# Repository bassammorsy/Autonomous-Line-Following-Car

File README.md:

# Autonomous-Line-Following-Car
Autonomous line-following robot with KiCad sensor array PCB design and PID motor control firmware on Arduino

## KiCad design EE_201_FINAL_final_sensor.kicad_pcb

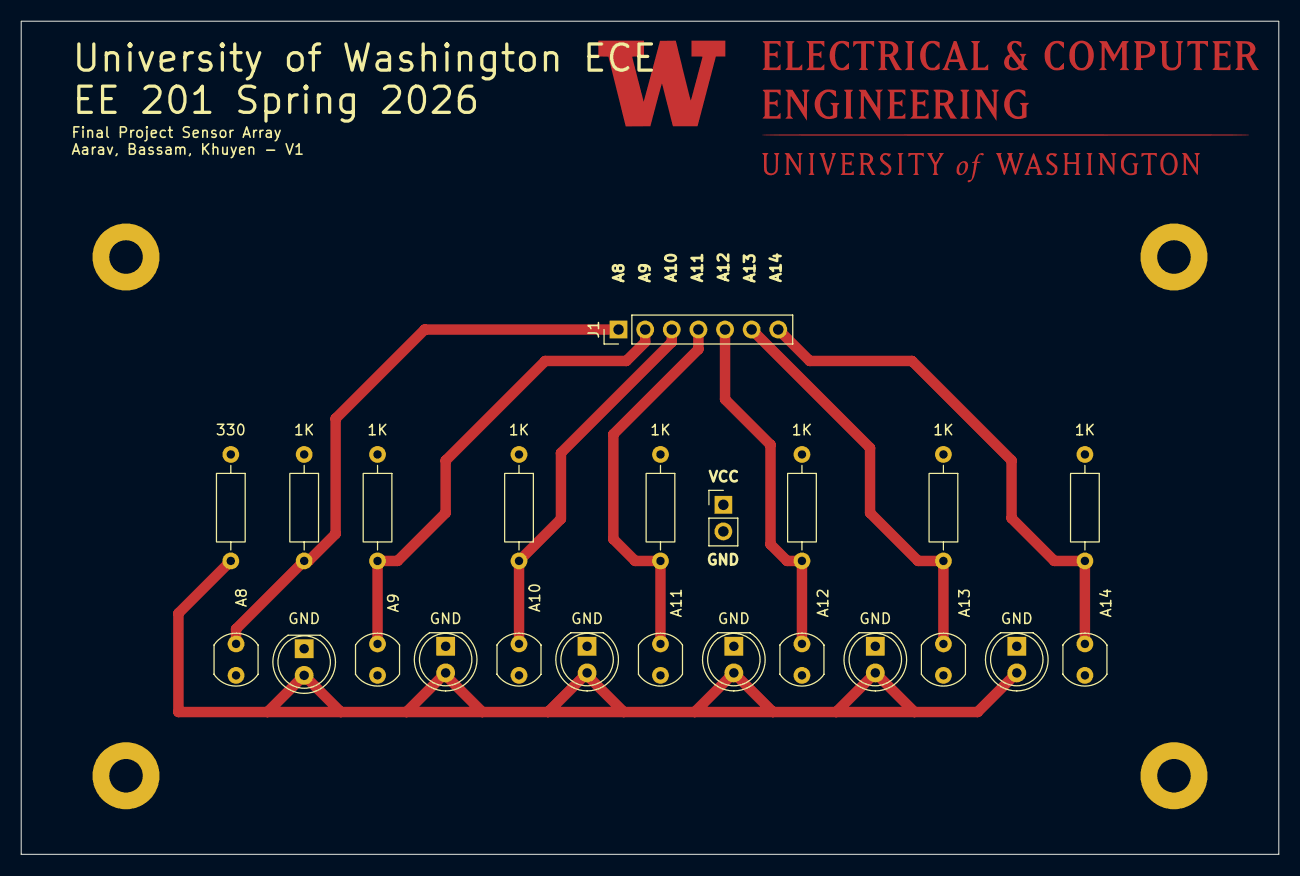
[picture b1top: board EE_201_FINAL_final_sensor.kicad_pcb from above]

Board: 2 copper layers, 120.0 x 79.5 mm, 28 parts (0 on the bottom side), 10 nets.

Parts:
1K: 1k; R_Axial_DIN0207_L6.3mm_D2.5mm_P10.16mm_Horizontal
A9: 1k; R_Axial_DIN0207_L6.3mm_D2.5mm_P10.16mm_Horizontal
D2, D3, D4, D5, D6: LED; LED_D5.0mm
GND: LED; LED_D5.0mm
H1, H2, H3, H4: MountingHole_Pad; MountingHole_3.2mm_M3_Pad
J1: Conn_01x07_Pin; PinHeader_1x07_P2.54mm_Vertical
R3, R4, R5, R6, R7: 1k; R_Axial_DIN0207_L6.3mm_D2.5mm_P10.16mm_Horizontal
R8, R9, R10, R11, R12, R13, R14: R_Photo; R_LDR_5.0x4.1mm_P3mm_Vertical
R15: 330; R_Axial_DIN0207_L6.3mm_D2.5mm_P10.16mm_Horizontal
VCC: Conn_01x02_Pin; PinHeader_1x02_P2.54mm_Vertical
logo: LOGO

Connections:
/A8: 1K.2, J1.1, R8.1
/A9: A9.2, J1.2, R9.1
/A10: J1.3, R3.2, R10.1
/A11: J1.4, R4.2, R11.1
/A12: J1.5, R5.2, R12.1
/A13: J1.6, R6.2, R13.1
/A14: J1.7, R7.2, R14.1
GND: D2.1 (K), D3.1 (K), D4.1 (K), D5.1 (K), D6.1 (K), GND.1 (K), H1.1, H2.1, H3.1, H4.1, R8.2, R9.2, R10.2, R11.2, R12.2, R13.2, R14.2, VCC.2
unnamed: D2.2 (A), D3.2 (A), D4.2 (A), D5.2 (A), D6.2 (A), GND.2 (A), R15.2
VCC: 1K.1, A9.1, R3.1, R4.1, R5.1, R6.1, R7.1, R15.1, VCC.1

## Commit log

2026-04-26 Add sensor array PCB design files and gerbers
2026-04-28 PCB and schematic pictures
2026-05-06 Added CAD of chassis
